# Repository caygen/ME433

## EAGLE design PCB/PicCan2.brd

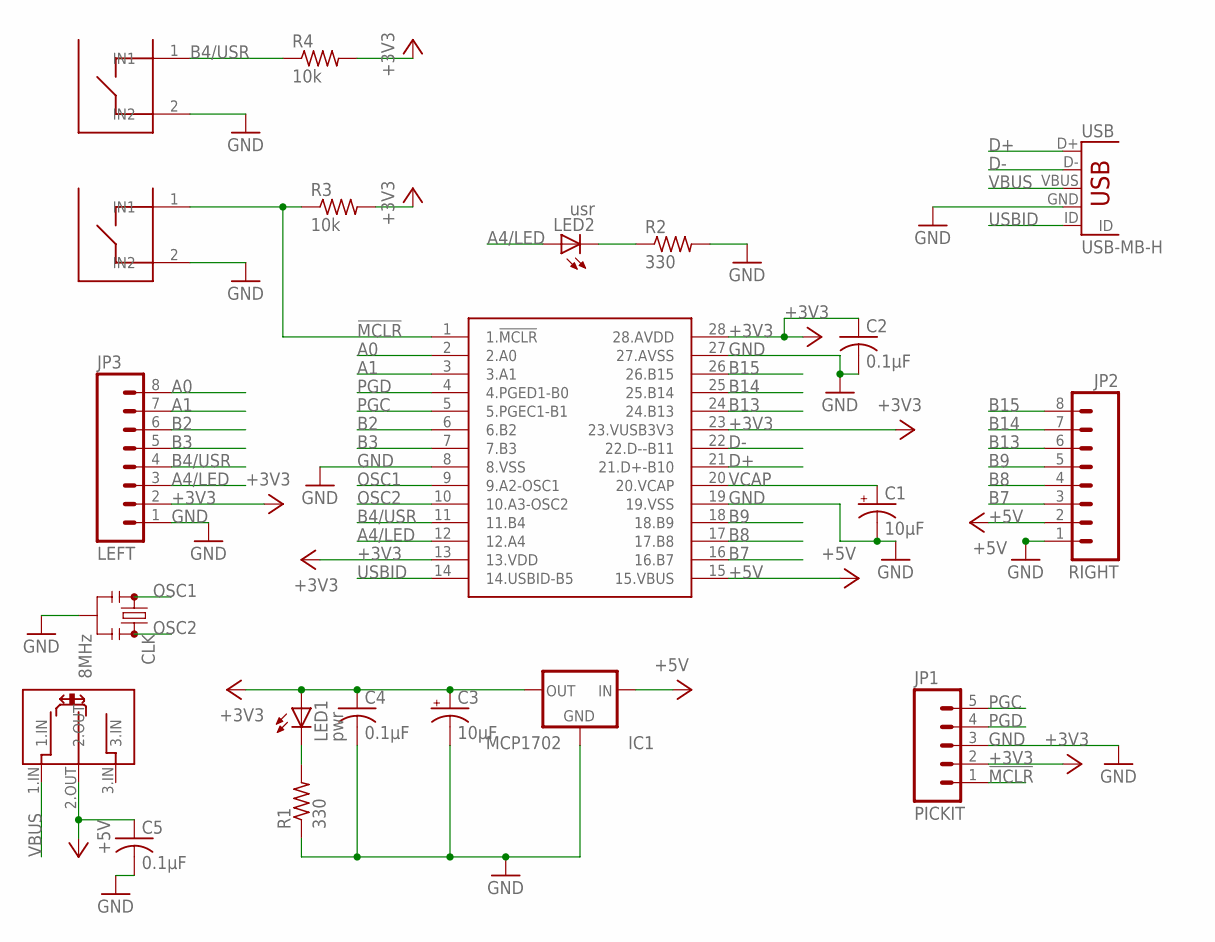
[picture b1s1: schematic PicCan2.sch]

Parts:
C1, C3: 10µF; B45181A
C2, C4, C5: 0.1µF; C025-025X050
CLK: 8MHz; RESONATOR-PTH
IC1: MCP1702; 79LXX
JP1: PICKIT; 1X05
JP2: RIGHT; 1X08
JP3: LEFT; 1X08
LED1: pwr; LED3MM
LED2: usr; LED3MM
PIC: PIC32MX250F128B; DIL28-3
R1, R2: 330; 0207/10
R3, R4: 10k; 0207/10
RESET: PUSHBUTTON; 1X020
U$2: SLDSWCH
USB: USB-MB-H
USER: PUSHBUTTON; 1X020

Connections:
!MCLR: JP1.1, PIC.1 (1.!MCLR), R3.1, RESET.1 (IN1)
+3V3: C2.1, C3.+, C4.1, IC1.OUT, JP1.2, JP3.2, LED1.A, PIC.13 (13.VDD), PIC.23 (23.VUSB3V3), PIC.28 (28.AVDD), R3.2, R4.2
+5V: C5.1, IC1.IN, JP2.2, PIC.15 (15.VBUS), U$2.2.OUT
A0: JP3.8, PIC.2 (2.A0)
A1: JP3.7, PIC.3 (3.A1)
A4/LED: JP3.3, LED2.A, PIC.12 (12.A4)
B2: JP3.6, PIC.6 (6.B2)
B3: JP3.5, PIC.7 (7.B3)
B4/USR: JP3.4, PIC.11 (11.B4), R4.1, USER.1 (IN1)
B7: JP2.3, PIC.16 (16.B7)
B8: JP2.4, PIC.17 (17.B8)
B9: JP2.5, PIC.18 (18.B9)
B13: JP2.6, PIC.24 (24.B13)
B14: JP2.7, PIC.25 (25.B14)
B15: JP2.8, PIC.26 (26.B15)
D+: PIC.21 (21.D+-B10), USB.D+
D-: PIC.22 (22.D--B11), USB.D-
GND: C1.-, C2.2, C3.-, C4.2, C5.2, CLK.2, IC1.GND, JP1.3, JP2.1, JP3.1, PIC.8 (8.VSS), PIC.19 (19.VSS), PIC.27 (27.AVSS), R1.1, R2.2, RESET.2 (IN2), USB.GND, USER.2 (IN2)
unnamed: LED2.K (C), R2.1
unnamed: LED1.K (C), R1.2
OSC1: CLK.1, PIC.9 (9.A2-OSC1)
OSC2: CLK.3, PIC.10 (10.A3-OSC2)
PGC: JP1.5, PIC.5 (5.PGEC1-B1)
PGD: JP1.4, PIC.4 (4.PGED1-B0)
USBID: PIC.14 (14.USBID-B5), USB.ID
VBUS: U$2.1.IN, USB.VBUS
VCAP: C1.+, PIC.20 (20.VCAP)

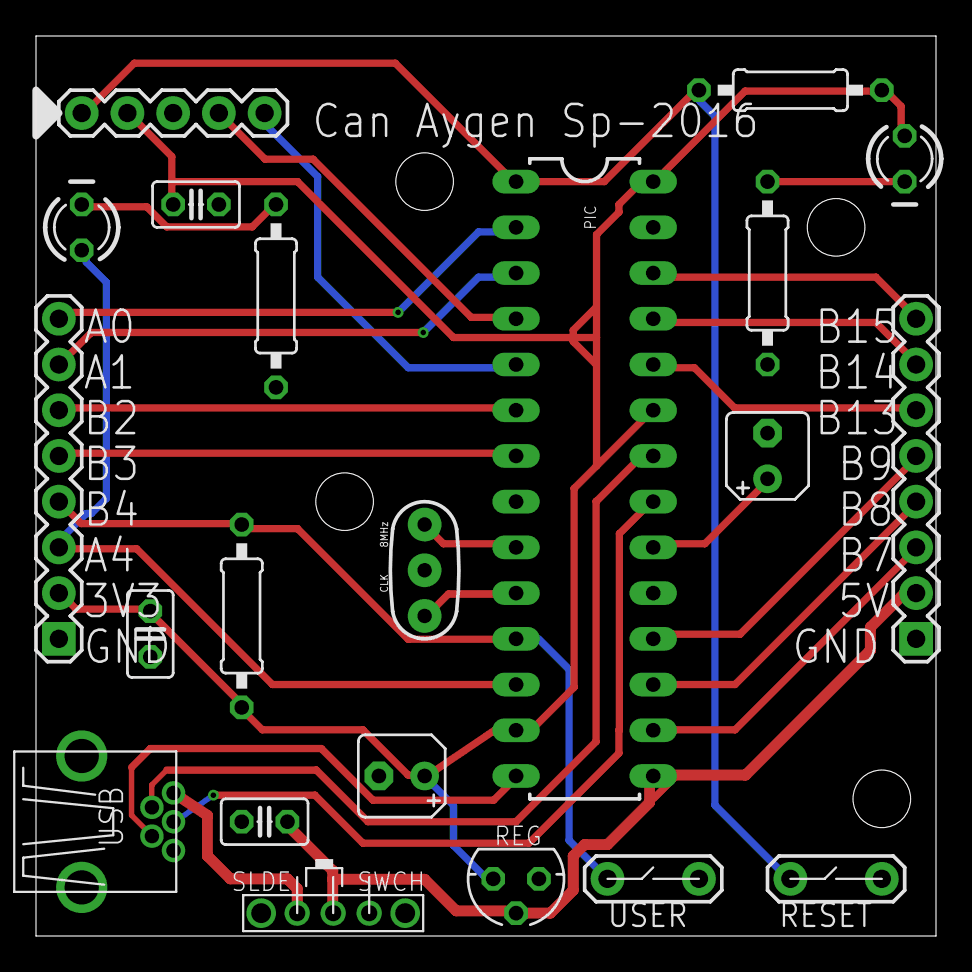
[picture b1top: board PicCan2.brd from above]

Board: 2 copper layers, 50.0 x 50.0 mm, 21 parts (0 on the bottom side), 27 nets.

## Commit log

2016-04-04 Create hw1
2016-04-04 Update hw1
2016-04-04 hw1 code
2016-04-04 deleted prev code
2016-04-04 started working on the code
2016-04-04 editing pragmas
2016-04-04 CLK SETTINGS
2016-04-04 DEVCFG3
2016-04-04 tris&lat
2016-04-04 lat/tris comment
2016-04-04 1000hztest
2016-04-04 led@1kHz
2016-04-04 tris
2016-04-04 reading port
2016-04-04 hw1done
2016-04-06 dunno what changed
2016-04-06 forgot the hand drawn schematic
2016-04-14 Ready to be checked before order
    Ready to be checked before order
2016-04-14 added library and safety margin for slide holes
    Ready to be checked before order
2016-04-14 Added drill holes
    Ready to be checked before order
2016-04-14 zipfile
    Ready to be checked before order
2016-04-21 still working on hw4
2016-06-03 bulk update of past stuff
2016-06-03 need to do green mask then done
2016-06-03 bulk update cont.
2016-06-06 bulk hw upload contd.
2016-06-06 hws cont'd
2016-06-06 PWM and Updated CAD
2016-06-07 tech cup done
2016-06-07 tech cup optimized and done :)
2016-06-07 app icon
2016-06-08 techcup final
2016-06-09 HWs complete + techcup photos
